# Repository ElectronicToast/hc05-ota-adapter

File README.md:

# HC-05 OTA Adapter

Adapter for HC-05 module for Arduino Bluetooth programming.

## Description

This is a small adapter board that breaks out an HC-05 Bluetooth module to a FTDI compatible pinout. Any AVR-based Arduino can be programmed via Bluetooth through this adapter by following the steps listed in either of the following tutorials:

- [DIY Arduino Bluetooth Programming Shield](https://makezine.com/projects/diy-arduino-bluetooth-programming-shield/) by Make Magazine
- [Inexpensively Program Your Arduino with Bluetooth](https://sites.google.com/site/wayneholder/inexpensively-program-your-arduino-via-bluetooth) by Wayne

This project is designed with KiCad EDA v.5.1.5. Documentation can be found under `/doc` and fabrication files under `/gerber`.

## Licensing

This project is released under the terms of the MIT License.

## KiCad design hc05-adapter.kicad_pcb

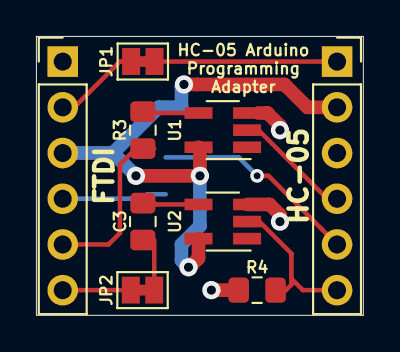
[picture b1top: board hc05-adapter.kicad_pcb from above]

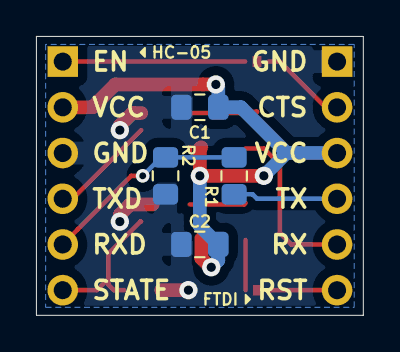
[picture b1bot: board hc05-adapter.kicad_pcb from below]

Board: 2 copper layers, 18.2 x 15.5 mm, 13 parts (4 on the bottom side), 13 nets.

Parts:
C1, C2, C3: 0.1uF; C_0805_2012Metric_Pad1.15x1.40mm_HandSolder
J1: Conn_01x06_0.1_Header; PinHeader_1x06_P2.54mm_Vertical
J2: Conn_01x06_0.1_Socket; PinSocket_1x06_P2.54mm_Vertical
JP1, JP2: SolderJumper_2_Bridged; SolderJumper-2_P1.3mm_Bridged_Pad1.0x1.5mm
R1: 1K; R_0805_2012Metric_Pad1.15x1.40mm_HandSolder
R2: 2K; R_0805_2012Metric_Pad1.15x1.40mm_HandSolder
R3: 100; R_0805_2012Metric_Pad1.15x1.40mm_HandSolder
R4: 10K; R_0805_2012Metric_Pad1.15x1.40mm_HandSolder
U1: 74LVC1G17; SOT-23-5_HandSoldering
U2: 74LVC1G14; SOT-23-5_HandSoldering

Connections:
+5V: C1.1, C2.1, J1.3, J2.2, U1.5, U2.5
/hc05-adapter/BT_EN: J2.1, JP1.1
/hc05-adapter/BT_RST: J2.6, R4.1, U2.2
/hc05-adapter/BT_RX: J2.5, R1.2, R2.1
/hc05-adapter/BT_TX: J2.4, U1.2
/hc05-adapter/ENABLE: J1.2, JP1.2
/hc05-adapter/RESET: J1.6, JP2.2
/hc05-adapter/RX: J1.5, R3.1
/hc05-adapter/TX: J1.4, R1.1
GND: C1.2, C2.2, J1.1, J2.3, R2.2, R4.2, U1.3, U2.3
unnamed: C3.1, JP2.1
unnamed: C3.2, U2.4
unnamed: R3.2, U1.4

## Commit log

2020-03-10 Add 1:1 fab prints
